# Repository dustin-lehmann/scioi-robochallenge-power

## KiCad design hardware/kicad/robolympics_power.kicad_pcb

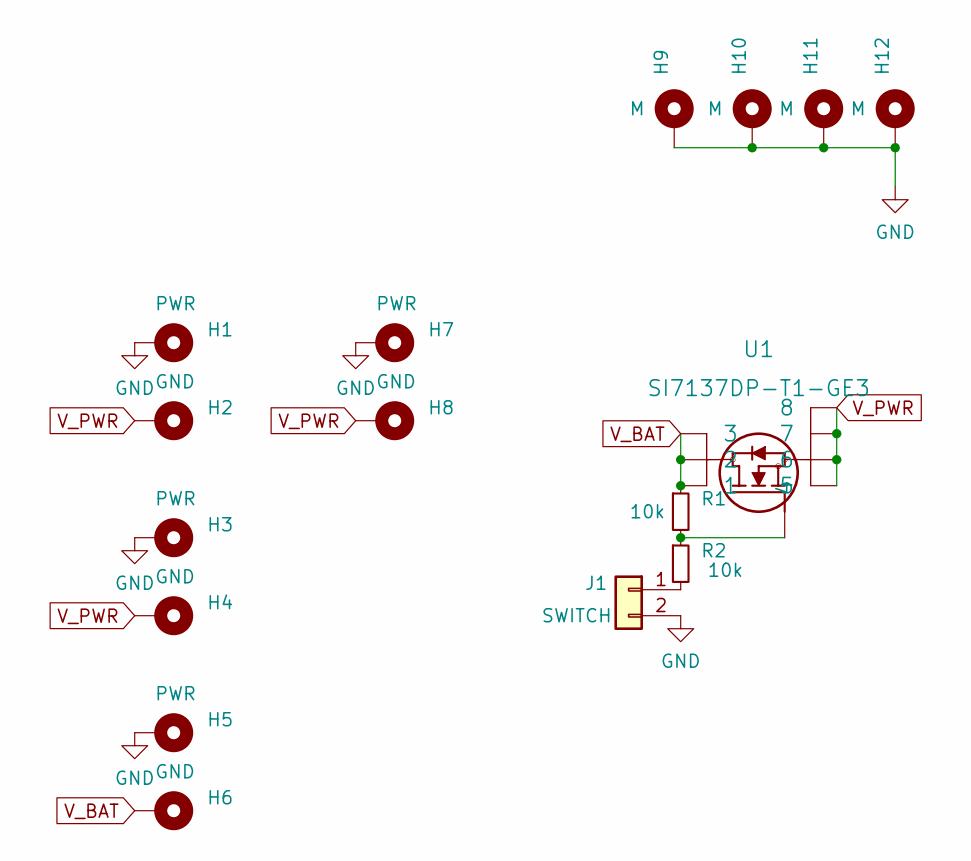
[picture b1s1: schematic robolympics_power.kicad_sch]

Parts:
H1, H3, H5, H7: PWR; MountingHole_4.3mm_M4_Pad_Via
H2, H4, H6, H8: GND; MountingHole_4.3mm_M4_Pad_Via
H9, H10, H11, H12: M; MountingHole_3.2mm_M3_DIN965_Pad
J1: SWITCH; PinHeader_1x02_P2.54mm_Vertical
R1, R2: 10k; R_0805_2012Metric
U1: SI7137DP-T1-GE3

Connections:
GND: H1.1, H3.1, H5.1, H7.1, H9.1, H10.1, H11.1, H12.1, J1.2
unnamed: J1.1, R2.2
unnamed: R1.2, R2.1, U1.4
V_BAT: H6.1, R1.1, U1.1, U1.2, U1.3
V_PWR: H2.1, H4.1, H8.1, U1.5, U1.6, U1.7, U1.8

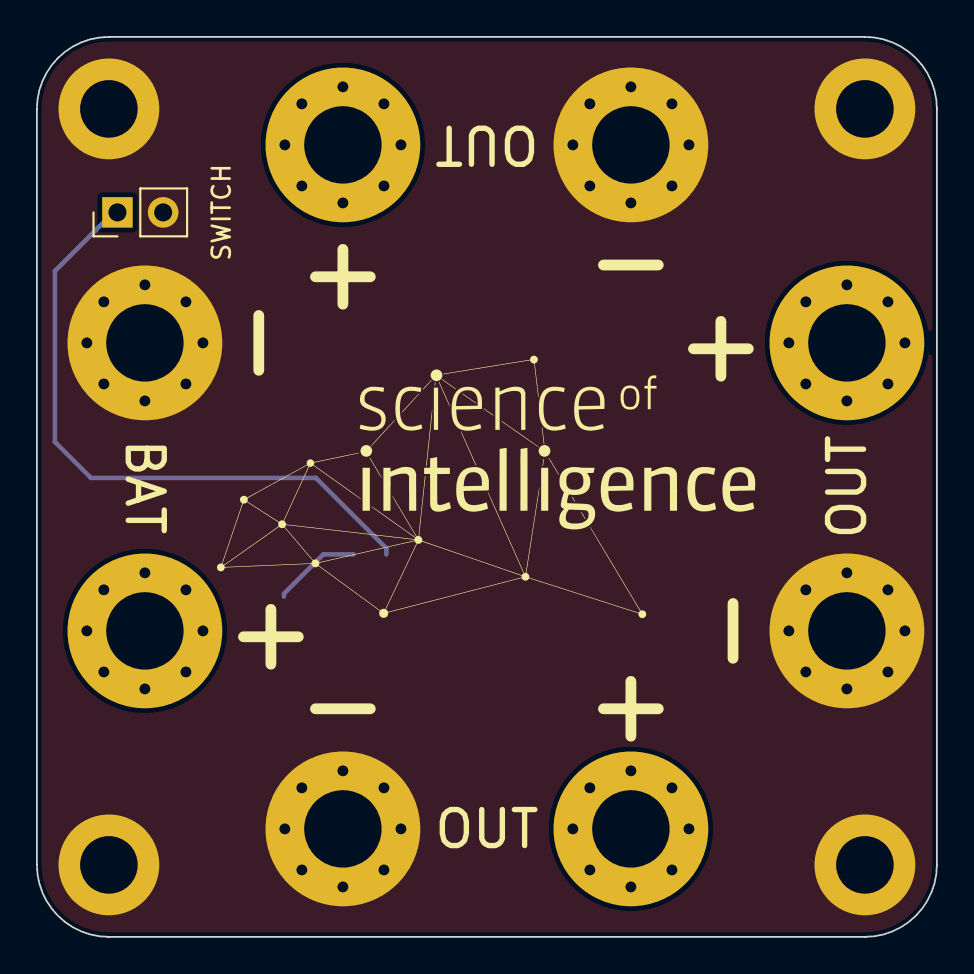
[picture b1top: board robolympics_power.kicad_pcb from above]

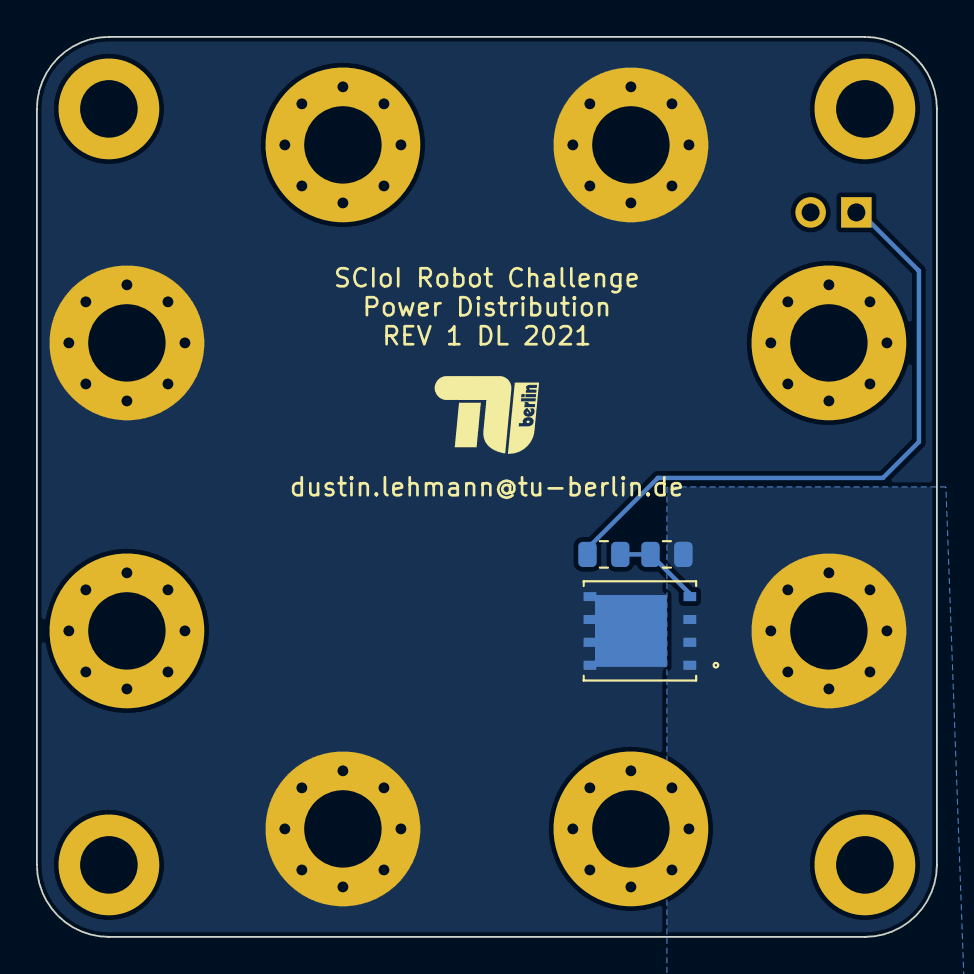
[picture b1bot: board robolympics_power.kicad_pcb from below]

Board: 2 copper layers, 50.0 x 50.0 mm, 16 parts (3 on the bottom side), 5 nets.

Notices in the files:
parts and their libraries:
Copyright 2021 Accelerated Designs. All rights reserved.
